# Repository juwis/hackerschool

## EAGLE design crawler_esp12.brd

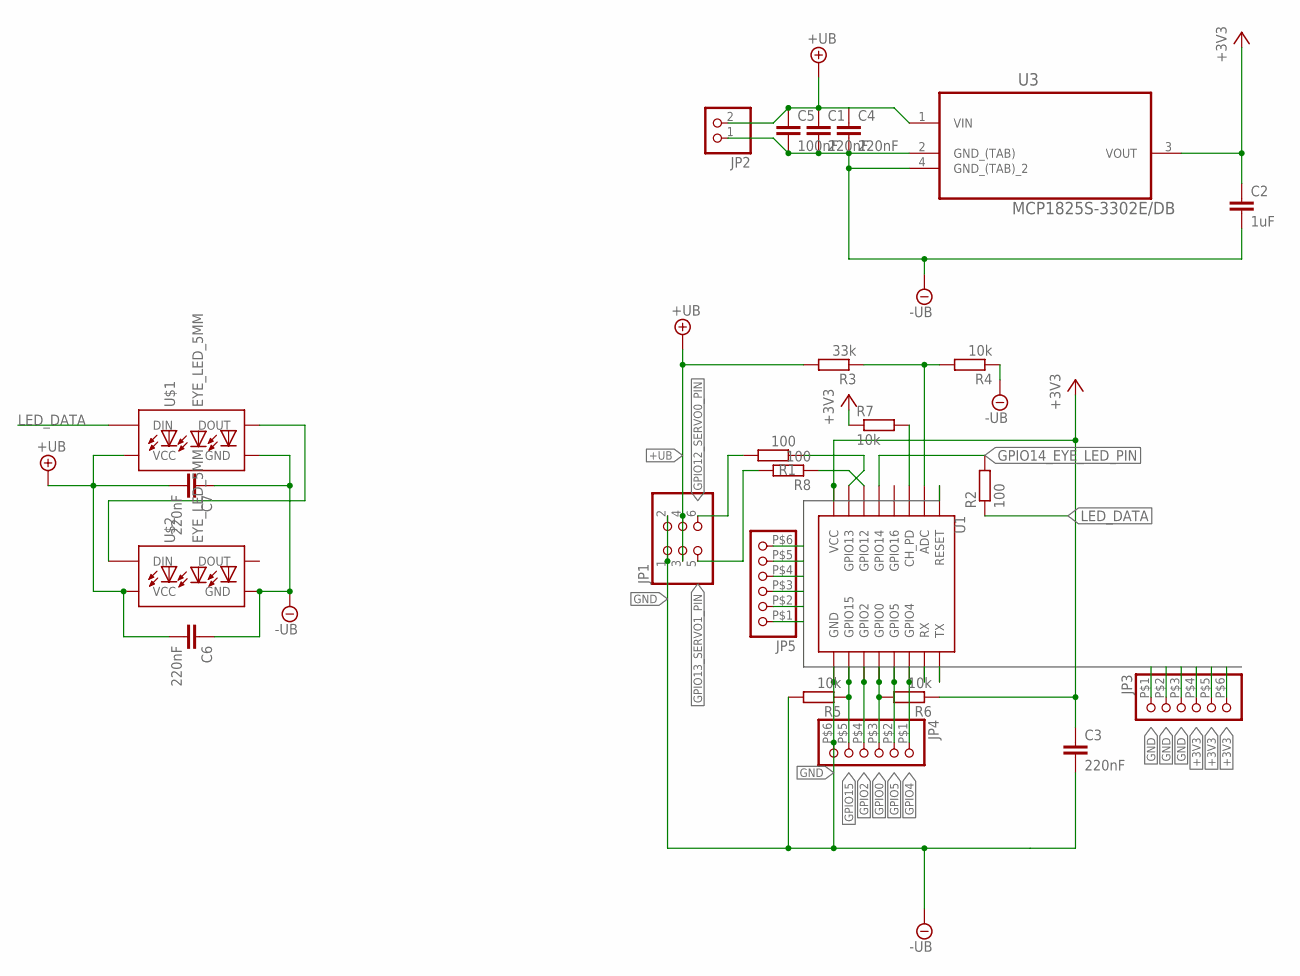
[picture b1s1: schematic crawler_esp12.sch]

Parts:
C1, C3, C4, C6, C7: 220nF; C0805
C2: 1uF; C0805
C5: 100nF; C0805
JP1: PINHD-2X3; 2X03
JP2: PINHD-1X2; 1X02
JP3, JP4, JP5: PINHD-1X6SMD; 1X06/90_SMD
R1, R2, R8: 100; R0805
R3: 33k; R0805
R4, R5, R6, R7: 10k; R0805
U1: ESP12SMD; ESP12-SMD
U3: MCP1825S-3302E/DB; SOT230P700X180-4N
U$1, U$2: EYE_LED_5MM

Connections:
+3V3: C2.1, C3.1, JP3.P$4 (4), JP3.P$5 (5), JP3.P$6 (6), JP5.P$1 (1), R6.1, R7.1, U1.VCC, U3.3 (VOUT)
+UB: C1.1, C4.1, C5.1, C6.2, C7.2, JP1.3, JP1.4, JP2.2, R3.2, U3.1 (VIN), U$1.5V (VCC), U$2.5V (VCC)
ADC: R3.1, R4.2, U1.ADC
ENABLE: R7.2, U1.CH_PD
GND: C1.2, C2.2, C3.2, C4.2, C5.2, C6.1, C7.1, JP1.1, JP1.2, JP2.1, JP3.P$1 (1), JP3.P$2 (2), JP3.P$3 (3), JP4.P$6 (6), JP5.P$6 (6), R4.1, R5.2, U1.GND, U3.2 (GND_(TAB)), U3.4 (GND_(TAB)_2), U$1.GND, U$2.GND
GPIO0: JP4.P$3 (3), JP5.P$2 (2), R6.2, U1.GPIO0
GPIO2: JP4.P$4 (4), U1.GPIO2
GPIO4: JP4.P$1 (1), U1.GPIO4
GPIO5: JP4.P$2 (2), U1.GPIO5
GPIO12_SERVO0_PIN: JP1.6, R1.2
GPIO13_SERVO1_PIN: JP1.5, R8.2
GPIO14_EYE_LED_PIN: R2.2, U1.GPIO14
GPIO15: JP4.P$5 (5), R5.1, U1.GPIO15
unnamed: U$1.DOUT, U$2.DIN
unnamed: R1.1, U1.GPIO13
unnamed: R8.1, U1.GPIO12
RESET: JP5.P$5 (5), U1.RESET
RX: JP5.P$4 (4), U1.RXD0 (RX)
TX: JP5.P$3 (3), U1.TXD0 (TX)

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
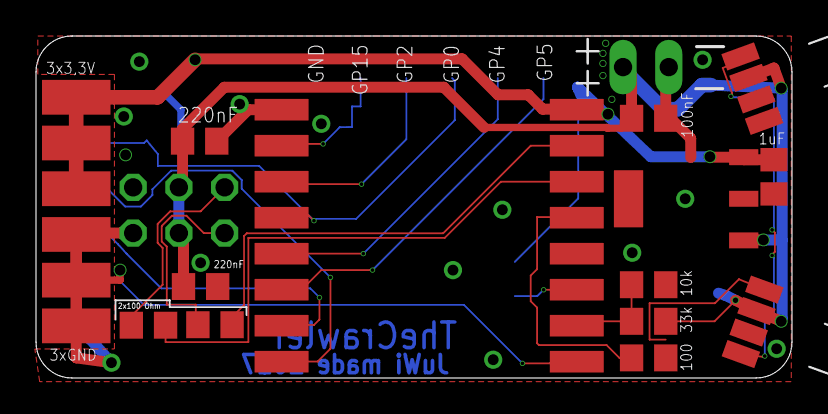
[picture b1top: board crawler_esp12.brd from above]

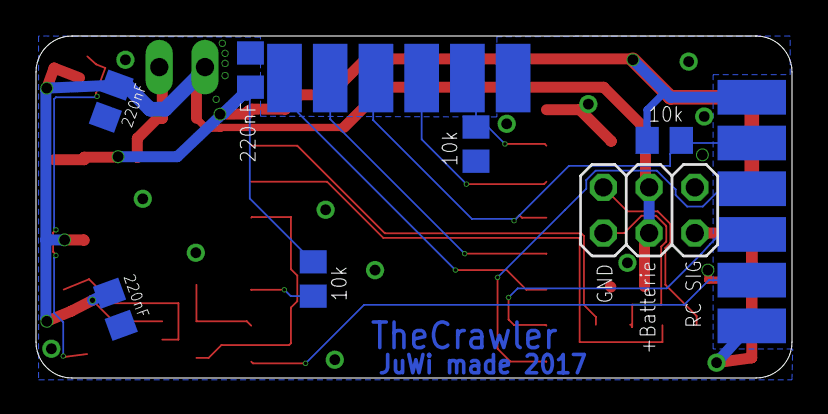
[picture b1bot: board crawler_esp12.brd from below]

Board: 2 copper layers, 42.0 x 19.0 mm, 24 parts (9 on the bottom side), 19 nets.

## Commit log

2017-03-21 First example of custom blocks.
2017-03-23 some pre finished hw designs
2017-04-02 Custom blocks for the machine and neopixel.
2017-04-27 Renamed the HTTP_Server and print to work on micropython.
2017-04-28 Some changes to use for micropython and return the result after a program is executed.
2017-05-07 GZIP compressed files added and extended the web server to load gz files if possible.
2017-05-10 External website added, font-awesome removed and toolbox xml file generated.
2017-05-10 Changed the path to the external files to github.io
2018-12-05 Adopted for python 3
2018-12-05 Run on python 3
2019-09-25 Examples changed to new event system.
2019-09-25 BugFix: changed the tab size for a more constistant behavior.
2019-09-25 Set a position of an Event is now possible
